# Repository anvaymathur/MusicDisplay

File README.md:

# MusicDisplay
A TFT touch screen music display that changes over bluetooth. Displays the current music playing and time.

## Description

The reason I wanted to build this is because, often when I listen to music while studying. If i ever want to change the 
music or adjust the volume, I get distracted looking at my phone. I also don't have headphones which can switch the music from
itself. So I wanted something where I can control the music and look at time and only important stuff, but I can't get distracted from something else.

## Features

* 3D Printed Case (TODO)
* TFT LCD Touch Screen for controls
* Interact with spotify over bluetooth
* EC11 Rorary Encoder for controlling volume
* USB-C connection for

## PCB

Custom PCB made in KiCad. Footprint for the ESP32 was built entirely by claude.

## Firmware

There is custom firmware for showing the current song, title, and artist. It shows the app name being used (ie. spotify) and time. Allows you to play and pause. It also shows the album picture and volume bar. It uses the knob 
to change the volumel, mute and unmute, and update the brightness of the screen. 

## BOM

| Item  | Description | # of Sets | #Pcs / Set | Price / Set (USD) | Item Total Price + Tax & Shipping (USD)| Supplier | URL |
| ----- | ----------- | --------- | ---------- | ----------------- | -------------------------------------- | -------- | -------| 
|Megaboard PCB Printing with JLCPCB | PCB | 1 | 5 | $5.20 | $12.11 | JLC PCB | https://kommodo.ai/iMpm5V022tOTxhFTwnaLW |
| SPI TFT LCD Touch Panel - 2.8" with Touch | TFT Touch Screen | 1 | 1 | $8.55 | $8.55 | AliExpress | https://www.aliexpress.com/item/32847628219.html?spm=a2g0o.productlist.main.2.33cf77b1gnrpY5&algo_pvid=0509a18b-44e0-4fb3-b00a-1c4f3944f9be&algo_exp_id=0509a18b-44e0-4fb3-b00a-1c4f3944f9be-1&pdp_ext_f=%7B%22order%22%3A%223864%22%2C%22spu_best_type%22%3A%22price%22%2C%22eval%22%3A%221%22%2C%22fromPage%22%3A%22search%22%7D&pdp_npi=6%40dis%21USD%217.65%217.65%21%21%217.65%217.65%21%402103128917932955914718541e0eb0%2112000033182735606%21sea%21CA%218292344353%21X%211%210%21n_tag%3A-29911%3Bd%3Adfeb2caa%3Bm03_new_user%3A-29895&curPageLogUid=1SAzQbczehUA&utparam-url=scene%3Asearch%7Cquery_from%3A%7Cx_object_id%3A32847628219%7C_p_origin_prod%3A |
| ESP32-S3 Supermini dev board | Microcontroller  | 1 | 1 | $3.49 | $3.49 | AliExpress | https://www.aliexpress.com/item/1005007523993589.html?spm=a2g0o.productlist.main.3.5b3b4090pWHUtf&algo_pvid=55434281-e44d-4b08-b09e-9082ebce36cd&algo_exp_id=55434281-e44d-4b08-b09e-9082ebce36cd-2&pdp_ext_f=%7B%22order%22%3A%22402%22%2C%22eval%22%3A%221%22%2C%22fromPage%22%3A%22search%22%7D&pdp_npi=6%40dis%21USD%213.49%213.49%21%21%213.49%213.49%21%402101f43b17933647155257133e0e12%2112000044263237981%21sea%21CA%218292344353%21X%211%210%21n_tag%3A-29911%3Bd%3Adfeb2caa%3Bm03_new_user%3A-29895&curPageLogUid=VGpB42wyyM2v&utparam-url=scene%3Asearch%7Cquery_from%3A%7Cx_object_id%3A1005007523993589%7C_p_origin_prod%3A |
| 360 Degree Rotary Encoder EC11 | Rotary Encoder | 1 | 3 | $1.19 | $1.19 | AliExpress | https://www.aliexpress.com/item/1005007644083514.html?spm=a2g0o.productlist.main.1.414b17573arSFE&algo_pvid=43460615-9ee4-41ed-ac14-7b29d6321f60&algo_exp_id=43460615-9ee4-41ed-ac14-7b29d6321f60-0&pdp_ext_f=%7B%22order%22%3A%224875%22%2C%22spu_best_type%22%3A%22price%22%2C%22eval%22%3A%221%22%2C%22fromPage%22%3A%22search%22%7D&pdp_npi=6%40dis%21USD%211.82%211.82%21%21%211.82%211.82%21%402101ca8b17933654439705871e0e50%2112000041630839409%21sea%21CA%218292344353%21X%211%210%21n_tag%3A-29911%3Bd%3Adfeb2caa%3Bm03_new_user%3A-29895&curPageLogUid=m3IskyDbyq9m&utparam-url=scene%3Asearch%7Cquery_from%3A%7Cx_object_id%3A1005007644083514%7C_p_origin_prod%3A |       |
| **Grand Total**: | | | | | $25.34|    

## Thank You

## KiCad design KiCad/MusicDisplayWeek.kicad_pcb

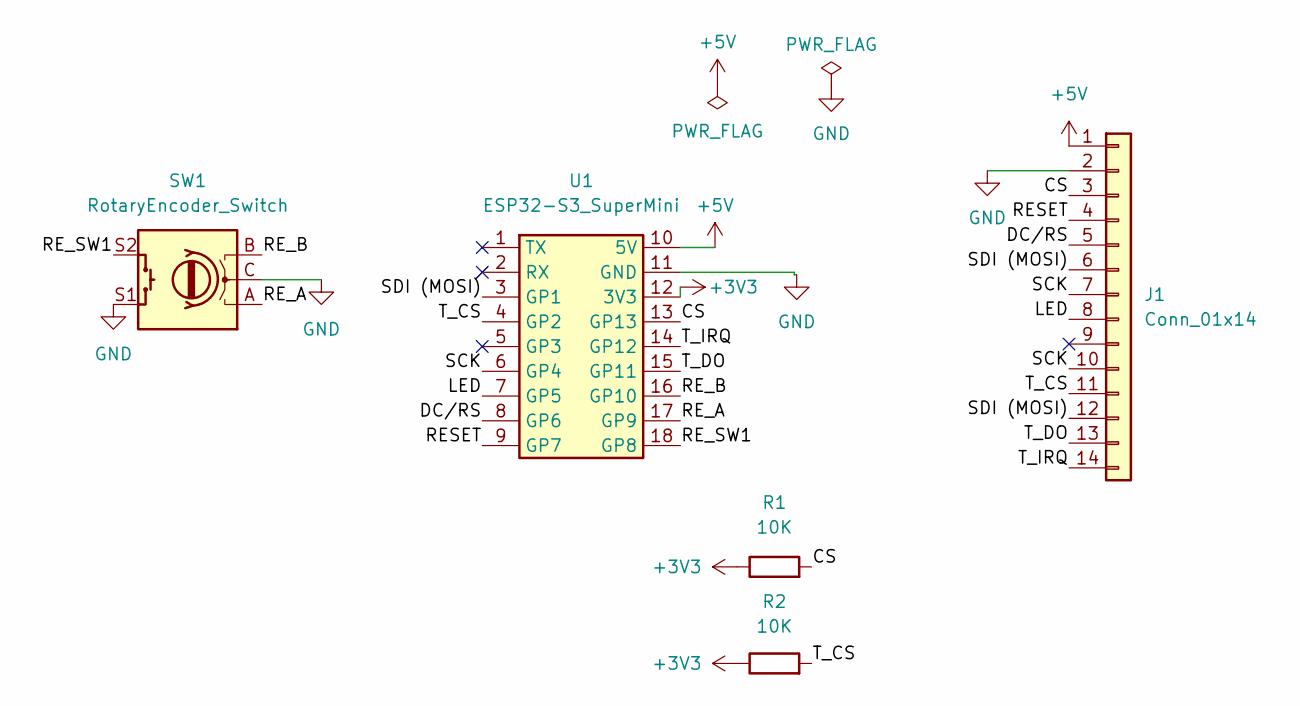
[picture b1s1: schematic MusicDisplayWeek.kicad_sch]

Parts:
J1: Conn_01x14; PinHeader_1x14_P2.54mm_Vertical
R1, R2: 10K; R_Axial_DIN0207_L6.3mm_D2.5mm_P7.62mm_Horizontal
SW1: RotaryEncoder_Switch; RotaryEncoder_Alps_EC11E-Switch_Vertical_H20mm
U1: ESP32-S3_SuperMini; ESP32-S3_SuperMini_2x9_Header

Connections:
+3V3: R1.1, R2.1, U1.12 (3V3)
+5V: J1.1, U1.10 (5V)
/CS: J1.3, R1.2, U1.13 (GP13)
/DC/RS: J1.5, U1.8 (GP6)
/LED: J1.8, U1.7 (GP5)
/RESET: J1.4, U1.9 (GP7)
/RE_A: SW1.A, U1.17 (GP9)
/RE_B: SW1.B, U1.16 (GP10)
/RE_SW1: SW1.S2, U1.18 (GP8)
/SCK: J1.7, J1.10, U1.6 (GP4)
/SDI (MOSI): J1.6, J1.12, U1.3 (GP1)
/T_CS: J1.11, R2.2, U1.4 (GP2)
/T_DO: J1.13, U1.15 (GP11)
/T_IRQ: J1.14, U1.14 (GP12)
GND: J1.2, SW1.C, SW1.S1, U1.11 (GND)

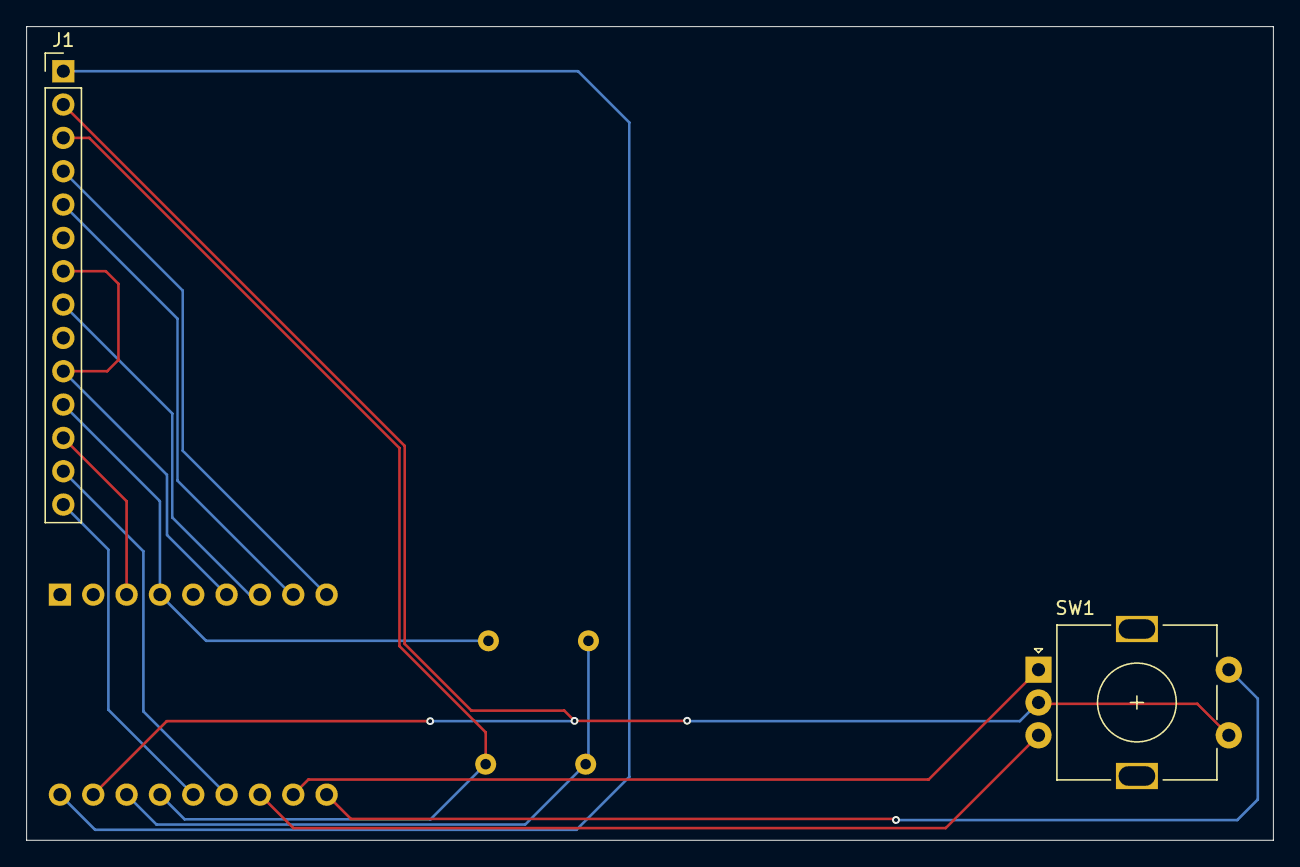
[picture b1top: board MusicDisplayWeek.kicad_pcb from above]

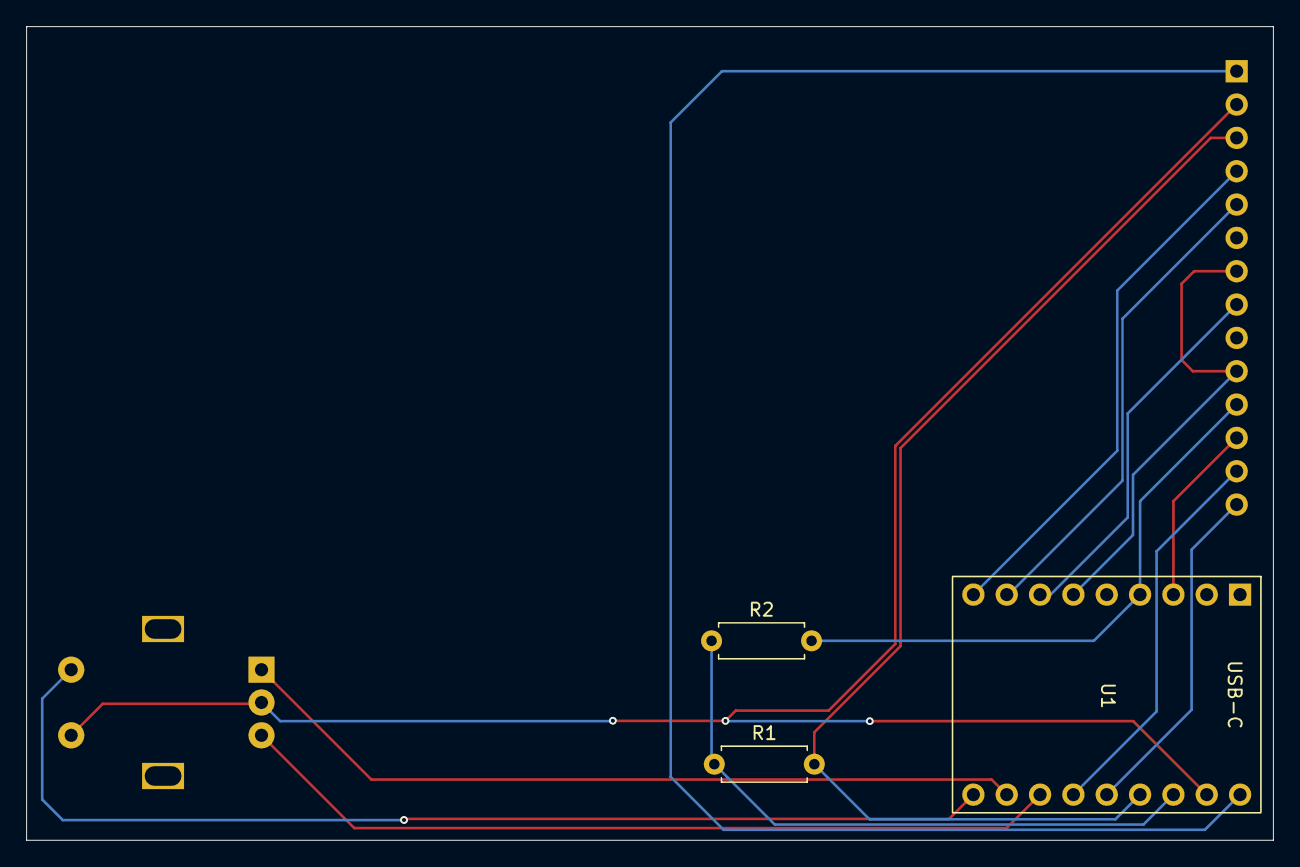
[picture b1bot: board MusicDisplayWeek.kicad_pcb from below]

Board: 2 copper layers, 95.0 x 62.0 mm, 5 parts (3 on the bottom side), 15 nets.
